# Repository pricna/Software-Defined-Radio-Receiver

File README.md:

# Software-Defined-Radio-Receiver
Software Defined Radio (SDR) receiver created in partial fulfillments of ENGR 357 "Engineering Electronics II" at Walla Walla University.

**Introduction:** This SDR receiver was designed to be simple and low cost, operate in the 10 MHz to 16 MHz frequency range, and also meet specific design criteria specified below. We ([Nate Price](https://github.com/pricna) and [Jared Evans](https://github.com/jred-KiCAD)), designed, assembled, and tested the SDR receiver to be used with a free open source SDR software, called Quisk. More information on the design, issues, testing, and software aspects of this project can be found on the [wiki page](https://github.com/pricna/Software-Defined-Radio-Receiver/wiki).

**Navigation:** 
- The Descriptions folder contains our circuit description for Miles
- The Images folder contains a variety of images of our board, PCB, and schematic
- The PCB Files folder contains some versions of our PCB, separated from the rest of the schematic files
- The Project Files folder contains our Bill of Materials and project files for v1.1
- The Schematic files folder contains pdfs of all of our schematic revisions, as well as project files for each of them
- The latest schematic can be found [here](https://github.com/pricna/Software-Defined-Radio-Receiver/tree/main/Schematic%20files/Project%20Files/v2.0/ENGR357_Project)

**Credits:** Much of this work builds on work described in [A Comparison of Affordable, Self-Assembled Software-Defined Radio Receivers Using Quadrature Sampling Down-Conversion](http://fweb.wallawalla.edu/~frohro/ClassHandouts/Electronics/A%20Comparison%20of%20Affordable,%20Self-Assembled%20%20Software-Defined%20Radio%20Receivers%20Using%20Quadrature%20Sampling%20Down-Conversion.pdf) by the authors [Caleb Froelich](https://github.com/froeca), [Konrad McClure](https://github.com/KonradMcClure), [Joshua Silver](https://github.com/JoshSilver8), [Jordyn Watkins](https://github.com/greenjacketgirl), and our professor, [Dr. Rob Frohne](https://github.com/frohro).

**Project Results:** We worked on two boards, one needs to have a FET replaced, which is a bit difficult with all the other connections we added to fix some PCB errors. It also might need further work, but it is unknown if there are more errors because the Arduino and Si5351 were not communicating. We were able to get the other board working. It produces I/Q signals 90 degrees out of face, has a sensitivity less than .1uV, and was successfully able to pick up signals when connected to the antenna with the Quisk software running. Take a look at [this video](https://www.youtube.com/watch?v=M_2Oau0vji8) to see the working radio!

## Further Information

(The information below is also covered in the [wiki page](https://github.com/pricna/Software-Defined-Radio-Receiver/wiki) (in sections). The wiki page also has some extra pages with information not in this document with milestones and generally useful information.

## 1. Hardware Design

## Block Diagram 

The block diagram was designed to help us get a better understanding of all the portions that needed to be designed for this project. Given that we had the benefit of seeing what other groups had previously worked on, figuring this out was relatively simple even though it does not fully match our final design.

## Bandpass Filter 

The bandpass filter was partially based on the work done previously by [Caleb Froelich](https://github.com/froeca) and [Konrad McClure](https://github.com/KonradMcClure). We used the same tool that they used, [rf-tools](https://rf-tools.com/lc-filter/), to calculate the necessary values for a 3rd-order Butterworth bandpass filter for a lower cutoff frequency of 10 MHz and an upper cutoff frequency of 16 MHz. The number of turns for the toroids was determined to be 3nH per turns^2 for the Ts7-6 and 4nH per turns^2 for the T50-6. The 2.15V voltage bias part on the end is used to center the incoming frequency between the maximum and minimum Tayloe Mixer input values, which adds noise, but we ultimately determined that having that part is more useful here. 

**Calculations:**

## Instrumentation Amplifier 

The instrumentation design is very similar to the [Caleb](https://github.com/froeca) and [Konrad](https://github.com/KonradMcClure) design. They designed it to work in a way such that the 0° and 180° signals, and the 90° and 270° are are differentially summed by the INA821ID Instrumentation Amplifiers.

## Tayloe Mixer 

The Tayloe mixer design is once again very similar. We decided that we did not need to re-determine how to set up the connections to get 0° on 00, 90° on 01, and so on.

## Voltage Smoother 

Once again, this is something the previous group used to reduce some of the noise that resulted from the constant switching in the computer. Since for this project, some additional noise reduction seemed particularly useful, we pulled also used it for our design.

## Local Oscillator 

As the previous group used a Johnson counter, the local oscillator needed to be updated for this project, since Dr. Frohne said it was unnecessary. A 3.3V connection was added to the SCL_3V and SDA_3V connections on the pins 4 and 5, a crystal was chosen because it was the frequency needed for the Si5351 chip, and the previous group did not use many surface mount components, so this schematic does. We also arbitrarily set our I/Q signals to CLK1 and CLK2. In a future redesign, it might be slightly easier to set up the software if the clocks are set to 0 & 1 instead.

## Voltage Converter 

A voltage converter was added because with the different voltages needed for the oscillator and Arduino, we wanted to be sure nothing was burned up because an incorrect voltage was used. This design comes from the [Adafruit Si5351 design](https://learn.adafruit.com/assets/18765). This was one of the places where we originally made an error in the schematic that made its way to the PCB.

## Lowpass Filter

Just like the bandpass filter, the lowpass filter was designed with assistance from online tools. This is one of the parts of our schematic that changed the most from the original design to the end result, but we ultimately decided on using a Sallen-Key Lowpass Filter that was calculated for a cutoff frequency of 100 kHz using [this online tool](http://sim.okawa-denshi.jp/en/OPseikiLowkeisan.htm). We also decided on using the LM4565 op amps for this (and the voltage smoother) because they were cheap and according to the datasheet, had a lower noise density than some of the other op amps we looked at.

## 2. Testing and Errors

## Basic Tests Done
The boards were constructed following our bring-up plan and Bill of Materials.

The first tests done were some basic continuity tests with a multimeter to confirm there were no major errors, such as a short between Vcc and ground, or shorts between pins on any of the smaller chips. We wound up eventually finding out that SDA and SCL were shorted, but that was determined after other tests were conducted.

One of the most useful tools for our testing was the program Logic, which we used with a Saleae Logic Analyzer connected to ground and the SDA and SCL pins on the Arduino. This was used because when we originally set up the [Arduino phase software](https://github.com/etherkit/Si5351Arduino/tree/master/examples/si5351_phase), we found that the I/Q signals were the default signals from our crystal. We updated the I2C address in the code from 0x60 to 0x62 to try and make it work, but that did not help. Hooking up the logic analyzer helped us determine that there were errors in our PCB because the Si5351 was not communicating with the Arduino. Those errors are detailed below in the **Errors** section.

When those errors were eventually fixed on Jared's board, we were able to get the proper devices communicating and confirm it with the logic analyzer. An oscilloscope was used to confirm that the Arduino code was changing the frequency, and properly offsetting the phase. We did not fix the communication issue on the other board, because that would require much more work (as detailed in the results page). The phase offset on Jared's board can be seen below. 

Also during our testing, the Bandpass filter was hooked up to a signal generator and oscilloscope to confirm that the connections were properly made. The results seemed good enough for the 10-16MHz range, so we decided it seemed to be working.

The final test needed before fully launching Quisk was to get the Arduino code that integrates with Quisk properly running. This wound up being a much more exhaustive undertaking than expected, because the code we used came from Dr. Frohne's untested code [here](https://github.com/frohro/IQ_SDR/tree/muSDR), and we struggled to get the correct phases output. Eventually, we determined with the help of Dr. Frohne that the frequency that set the proper phases needed to be multiplied by 100, and several instances of clocks 0&1 needed to be changed to clocks 0&2. With that updated, we were able to get the phases properly set.

## Errors 
Revealed by the testing process

Below are some images of some shorts that were discovered in our PCB. The appearance of these shorts was because of errors made in both our schematic and PCB. And since I (Nate) made the schematic, and Jared made the PCB, and we did not carefully check each others' work, we did not catch any obvious errors, such as the fact that SDA and SCL were obviously shorted. 

Here are some of the errors in the schematic that led to the errors in the PCB, and what was changed to fix them:

**Oscillator:**

As can be seen in the pictures above, pull-up resistors were incorrectly used. 

**Voltage Converter:**

As can be seen, an incorrect adjustment to the resistors in the Adafruit voltage converter was made. This was one of the bigger issues for how our PCB turned out.

## 3. Software
(and simulations)

## Simulations

We simulated our work using LTspice. Much of this work is based on the work previously done by Dr. Frohne and the other groups, but these simulations can be found [here](https://github.com/pricna/Software-Defined-Radio-Receiver/tree/main/LTspice%20Simulation%20Files) in the repository. Jared primarily focused on getting the simulations going. The following is an LTspice screenshot of a noise simulation that seemed to get decent results. The instrumentation amplifiers used are not the ones we used because of difficulties in finding the proper ones, and we did not fully integrate everything all of our circuitry into all of our simulations.

## Logic

As mentioned in the Testing and Errors page, the program Logic was used to check I2C signals. To set it up, hook up ground and SDA/SCL connections to a logic analyzer, set up an I2C analyzer in the software, load the Arduino phase code with the correct I2C address, and then press run in the software. It is a good idea to zoom out while it is running to confirm that signals are coming in, and then stop it and zoom in to check the signal. This is what it looks like when the I2C there is no acknowledgement.

## Arduino

The Arduino code was also mentioned previously on the Testing and Errors page, so to reiterate some of what was said. To test just the phase of the I/Q signals, [this example code can be used](https://github.com/etherkit/Si5351Arduino/tree/master/examples/si5351_phase). To use it with the board designed for this project, instances of clocks 0 & 1 need to be changes to clocks 1 & 2. Then for the overall Quisk code, modifications had to be made to Dr. Frohne's code to get it working with the code. Once again the clocks had to be changed, and some frequencies updated. Here is a screenshot of a portion of the changed code.

## Quisk

To set up Quisk, follow the installation steps detailed on [this page](https://james.ahlstrom.name/quisk/docs.html#Installation). Once Quisk is able to be executed, set up a softrock fixed radio with the quisk_conf_openradio.py config file. The changes made to the config file depend on the OS, but for this project, we set openradio_serial_port = "COM3" which is where the Arduino was plugged into the computer. We also changed the baud rate on the port to 57600 to match the baud rate in the software. We found that it is much easier to use Quisk if the soundcard and Arduino are plugged into a computer/laptop with multiple ports. If Quisk is properly set up, adjusting the frequency should adjust the I/Q frequencies in the board, which we confirmed with the oscilloscope. With that working, and an antenna set up, we were able to get good results, such as this:

Also note that with the version of the software we were using, we incorrectly got error messages when there were no errors when we launched Quisk. Some of the Quisk setup steps were glossed over a little bit, so for more information on that either look at the installation instruction link above, or check [Konrad McClure's documentation](https://github.com/KonradMcClure/SDR_Receiver) for some additional useful information.

## 4. Results

## Nate's results
The software was changed to set the I2C address to 0x62 as per the data sheet for our Si5351. After connecting the logic analyzer, and learning that there was no acknowledgement, and trying to make additional corrections, it became clear that there was some other issue in the board.

Dr. Frohne helped determine that the issue was with one of the FETs that we had soldered several connections to.
The best ways to fix the error are:​
- Design a new PCB, have it made, solder everything again​.
- Use one of the extra broken PCB’s to start again, knowing which fixes are needed​.

Either way requires a lot of time desoldering and then soldering again​. Ultimately decided to make sure Jared’s board worked​, which wound up requiring a large amount of collaboration. The board in it's current, broken state are shown below.

## Jared's results

We used the logic analyzer to confirm that on this board, the Si5351 communicates with Arduino. We used an oscilloscope to confirm that we could set the phases using [Arduino code](https://github.com/etherkit/Si5351Arduino/tree/master/examples/si5351_phase). On the signal generator we hooked up to the board, we found the sensitivity to be less than 0.1uV. Also, with Quisk set up, we found the image rejection to be approximately 3 dB. Though the most important result, is that we were able to tune Quisk to pick up a signal with the antenna connected. 

A video of a signal we picked up can be found [here](https://www.youtube.com/watch?v=M_2Oau0vji8).

And a picture of the fully constructed and working board can be found below:

Finally, here is a picture of Quisk running, and picking up a signal:

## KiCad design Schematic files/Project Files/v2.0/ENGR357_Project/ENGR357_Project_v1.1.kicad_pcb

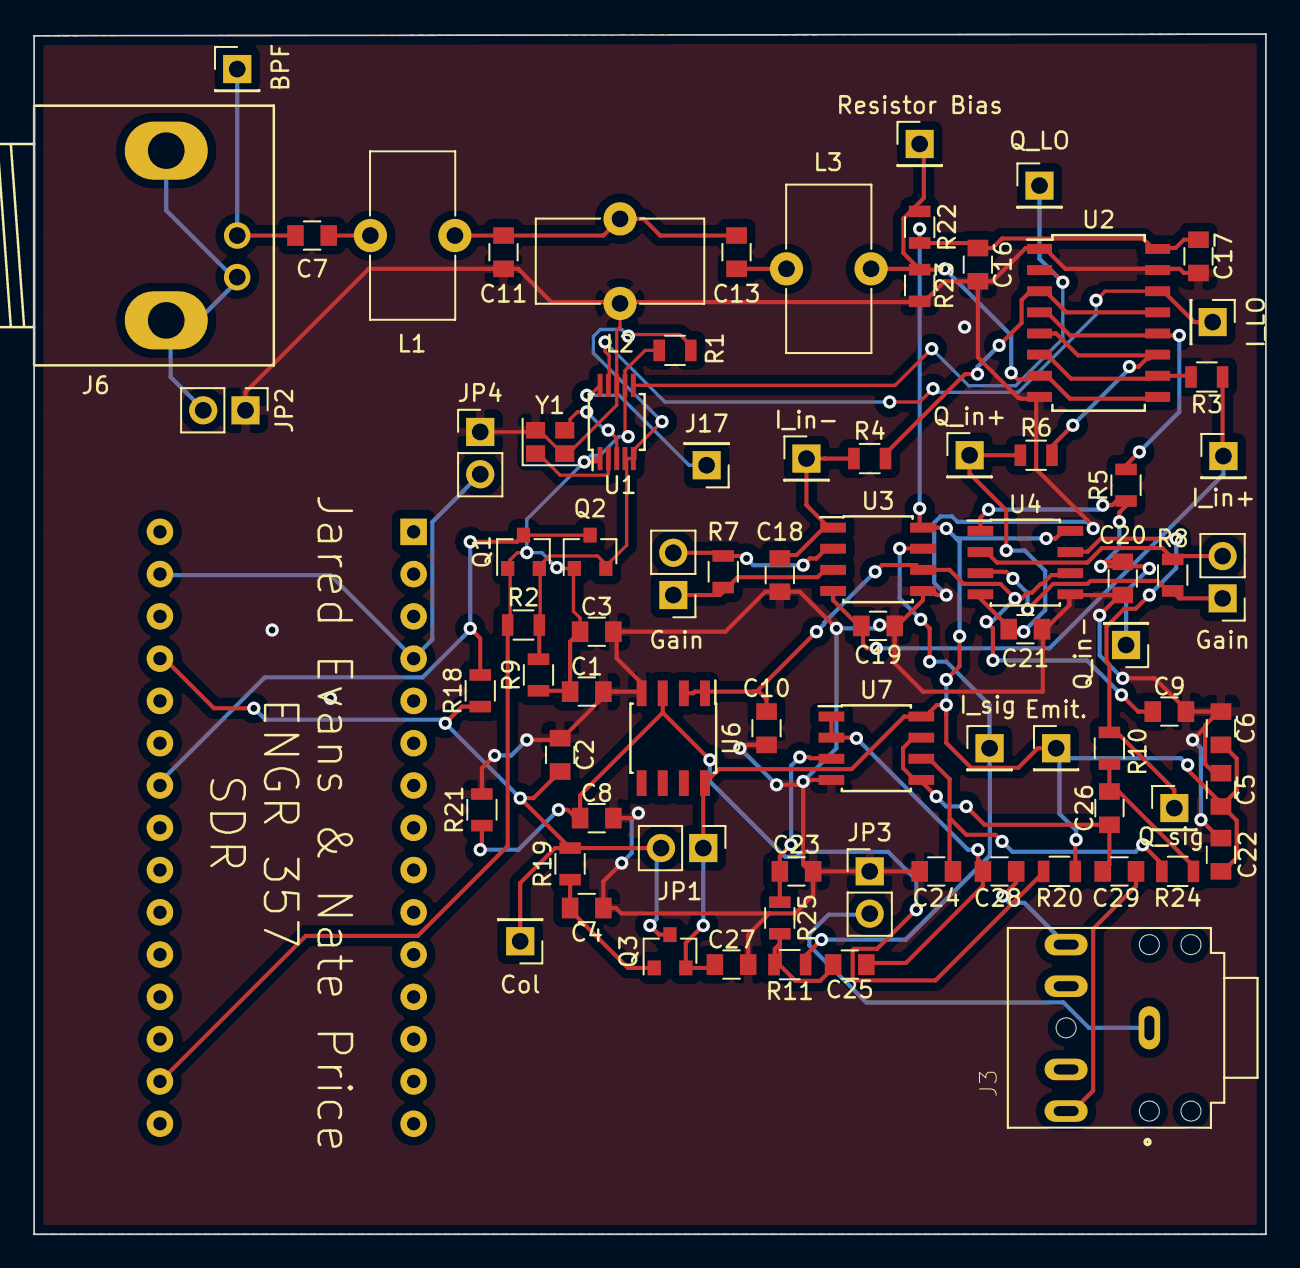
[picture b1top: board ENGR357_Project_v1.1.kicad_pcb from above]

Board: 2 copper layers, 74.0 x 72.1 mm, 80 parts (1 on the bottom side), 44 nets.

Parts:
A1: Arduino_Nano_v3.x; Arduino_Nano
BPF: IQ_SDR-rescue_Conn_01x01-Connector_Generic-IQ_SDR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; Pin_Header_Straight_1x01_Pitch2.54mm
C1, C2, C3, C5, C6, C8, C16, C17: .1u; C_0805
C4: 10u; C_0805
C7, C13: 120pF; C_0805
C9, C10, C22, C27: .1uF; C_0805
C11: 1.1nF; C_0805
C18, C19, C20, C21: 3900p; C_0805
C23, C24, C25, C26: 100pF; C_0805
C28, C29: 10uF; C_0805
Col: IQ_SDR-rescue_Conn_01x01-Connector_Generic-IQ_SDR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; Pin_Header_Straight_1x01_Pitch2.54mm
Emit.: IQ_SDR-rescue_Conn_01x01-Connector_Generic-IQ_SDR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; Pin_Header_Straight_1x01_Pitch2.54mm
Gain: Conn_01x02_Female; Pin_Header_Straight_1x02_Pitch2.54mm
Gain : Conn_01x02_Female; Pin_Header_Straight_1x02_Pitch2.54mm
I_LO: IQ_SDR-rescue_Conn_01x01-Connector_Generic-IQ_SDR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; Pin_Header_Straight_1x01_Pitch2.54mm
I_in+: IQ_SDR-rescue_Conn_01x01-Connector_Generic-IQ_SDR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; Pin_Header_Straight_1x01_Pitch2.54mm
I_in-: IQ_SDR-rescue_Conn_01x01-Connector_Generic-IQ_SDR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; Pin_Header_Straight_1x01_Pitch2.54mm
I_sig: IQ_SDR-rescue_Conn_01x01-Connector_Generic-IQ_SDR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; Pin_Header_Straight_1x01_Pitch2.54mm
J3: 35RAPC4BHN2; SWITCHCRAFT_35RAPC4BHN2
J6: Conn_Coaxial; BNC_Socket_TYCO-AMP
J17: IQ_SDR-rescue_Conn_01x01-Connector_Generic-IQ_SDR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; Pin_Header_Straight_1x01_Pitch2.54mm
JP1, JP3, JP4: Jumper_NC_Small-Device; Pin_Header_Straight_1x02_Pitch2.54mm
JP2: Jumper_NC_Small; Pin_Header_Straight_1x02_Pitch2.54mm
L1, L3: 1.3uH; L_Toroid_Vertical_L10.0mm_W5.0mm_P5.08mm
L2: 150nH; L_Toroid_Vertical_L10.0mm_W5.0mm_P5.08mm
Q1, Q2: BSS138; SOT-23
Q3: MMBT2222A-MMBT2222A; SOT-23
Q_LO: IQ_SDR-rescue_Conn_01x01-Connector_Generic-IQ_SDR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; Pin_Header_Straight_1x01_Pitch2.54mm
Q_in+: IQ_SDR-rescue_Conn_01x01-Connector_Generic-IQ_SDR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; Pin_Header_Straight_1x01_Pitch2.54mm
Q_in-: IQ_SDR-rescue_Conn_01x01-Connector_Generic-IQ_SDR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; Pin_Header_Straight_1x01_Pitch2.54mm
Q_sig: IQ_SDR-rescue_Conn_01x01-Connector_Generic-IQ_SDR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; Pin_Header_Straight_1x01_Pitch2.54mm
R1, R2, R7, R8, R19: 1k; R_0805
R3, R4, R5, R6: 50; R_0805
R9, R18, R20, R21, R22, R23: 10k; R_0805
R10, R11, R24, R25: 12k; R_0805
Resistor Bias: IQ_SDR-rescue_Conn_01x01-Connector_Generic-IQ_SDR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; Pin_Header_Straight_1x01_Pitch2.54mm
U1: Si5351A-B-GT; MSOP-10_3x3mm_Pitch0.5mm
U2: SN74CBT3253; SOIC-16W_5.3x10.2mm_Pitch1.27mm
U3, U4: INA821ID; SOIC-8_3.9x4.9mm_Pitch1.27mm
U6, U7: LM4562; SOIC-8_3.9x4.9mm_Pitch1.27mm
Y1: CX3225; Crystal_SMD_2520-4pin_2.5x2.0mm

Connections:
+3V3: A1.17, C1.1, C3.1, Q1.1, Q2.1, R1.1, R2.1, R9.1, U1.1, U1.7
+4.3V: C5.2, C6.2, C16.2, C17.1, C22.1, C27.1, Emit..1, JP1.1, Q3.2, R20.1, R22.2, U2.16, U3.8, U4.8, U6.8, U7.8
+5V: A1.27, C2.2, Col.1, JP1.2, Q3.3, R18.1, R19.2
/BP_Filter_o: L3.2, R22.1, R23.2, Resistor Bias.1, U2.7, U2.9
/I_LO: I_LO.1, U1.9, U2.14
/Q_LO: Q_LO.1, U1.6, U2.2
/SCL_3V: Q1.2, Q2.2, R1.2, R2.2, R9.2, U1.4, U1.5
/SCL_5V: A1.23, A1.24, Q1.3, Q2.3, R18.2
GND: C1.2, C2.1, C3.2, C4.1, C5.1, C6.1, C8.2, C9.2, C10.2, C11.2, C16.1, C17.2, C18.2, C19.2, C20.2, C21.2, C22.2, C23.1, C24.1, C27.2, JP2.1, JP3.1, JP4.1, L2.2, R21.2, R23.1, U1.8, U2.1, U2.8, U2.15, U3.5, U4.5, U6.4, U7.4, Y1.2, Y1.4
GNDA: C9.1, C10.1, U3.6, U4.6, U6.1, U6.2
unnamed: A1.4, A1.29, JP4.2
unnamed: C4.2, Q3.1, R19.1
unnamed: C7.1, L1.1
unnamed: BPF.1, C7.2, J6.1
unnamed: C8.1, R20.2, R21.1, U6.3
unnamed: C11.1, C13.1, L1.2, L2.1
unnamed: C13.2, L3.1
unnamed: C18.1, I_in-.1, R4.1, U3.1
unnamed: C19.1, I_in+.1, R3.1, U3.4
unnamed: C20.1, Q_in-.1, R5.1, U4.1
unnamed: C21.1, Q_in+.1, R6.1, U4.4
unnamed: C23.2, R25.1, U7.3
unnamed: C24.2, R24.1, U7.6
unnamed: C25.1, C28.1, U7.1, U7.2
unnamed: C25.2, R11.1, R25.2
unnamed: C26.1, C29.1, U7.5, U7.7
unnamed: C26.2, R10.1, R24.2
unnamed: C28.2, J3.2
unnamed: C29.2, J3.3
unnamed: Gain.1, R7.2, U3.3
unnamed: Gain.2, R7.1, U3.2
unnamed: Gain.1, R8.2, U4.3
unnamed: Gain.2, R8.1, U4.2
unnamed: J3.1, JP3.2
unnamed: J6.2, JP2.2
unnamed: I_sig.1, R11.2, U3.7
unnamed: Q_sig.1, R10.2, U4.7
unnamed: J17.1, U1.10
unnamed: R3.2, U2.6, U2.10
unnamed: R4.2, U2.3, U2.13
unnamed: R5.2, U2.4, U2.12
unnamed: R6.2, U2.5, U2.11
unnamed: U1.2, Y1.1
unnamed: U1.3, Y1.3

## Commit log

2021-04-12 Create Milestone
2021-04-12 Create Sim
2021-04-12 Create LICENSE
2021-04-14 Create temp
2021-04-14 Create tmp
2021-04-14 Add files via upload
    Added Circuit Description for Milestone 3
2021-04-14 Add files via upload
    Added preliminary SDR Schematic PDF file
2021-04-19 Added schematic files for v0.2
    Changes still need to be made.
2021-04-19 Added v0.2 schematic
2021-04-23 Added milestone 4 noise sims
2021-04-23 Added schematic files for version 0.4
2021-04-25 Moved v0.1 files to there own directory
2021-04-25 Added v1.0 Schematic Files
2021-04-25 Simulates the main circuit setup
2021-04-27 Updated according to suggestions
2021-04-27 Added v1.1 schematic files
2021-04-29 Create PCB Files
2021-04-29 removed file
2021-04-29 Added PCB Files directory
2021-06-01 Added PCB and schematic images
2021-06-06 Uploaded Block Diagram
2021-06-06 Added images of calculations
2021-06-07 v2.0 schematic added
    Make sure to open the right version, because the files are a bit disorganized
2021-06-09 Added more pictures
2021-06-09 Added another image
